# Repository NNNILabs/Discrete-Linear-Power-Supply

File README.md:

# Discrete Linear Power Supply
Fully discrete dual tracking linear supply with CC and CV

## Why?
I was not fully satsified with my previous linear supply based on op-amps, so I decided that I was done with the "black box" approach and decided to go fully discrete this time. 

## How?
The linear supply consists of three parts - the reference, the constant voltage circuit and the constant current circuit. The positive and negative parts are more or less mirror images of each other. 

### The References
The reference element here is a zener diode. The circuit does not operate using reference voltages, but rather reference currents supplied by degenerated PNP/NPN current sources/sinks. 
The Zener diode sets the voltage across the emitter resistors of the buffer transistors, forming current sources/sinks. This current is mirrored and fed back into the Zener diodes, creating a stable closed-loop reference. 

### The Current Limiting Circuitry
The current limiting circuitry is a mix of at least three different circuit ideas from various sources - the emitter input differential amplifier from The Art of Electronics: The X Chapters, the ZDS1009 IC, and the current comparator from Designing Analog Chips. The easiest explanantion is that a constant voltage is set across the left degeneration resistor of the mirror ladder, and when the shunt exceeds this voltage, the output transistor is turned on, pulling the output MOSFET low till the current setpoint is reached. The limit threshold is set by a constant current through the set potentiometer, the voltage across which is mirrored on a resistor which sets the current through the degeneration resistor, the voltage across whic determines the shunt voltage threshold.

### The Voltage Regulating Circuitry 
Again an example of emitter input differential amplifiers - the circuit tries to make the emitter voltages the same and drives the output MOSFET accordingly. The voltage is set by a constant current through the set potentiometer. 

### Notes
- Dual tracking is achieved by sinking/sourcing the same current through the set potentiometers, which creates a voltage across it based on the resistance. Since the current source outputs would otherwise be "floating" (i.e., the voltage across the shunt is constant but there is no guarantee as to where it is relative to ground), two 1M balance resistors connected to ground are added. 
- The value of the compensation resistor and capacitor between the gate and drain of each MOSFET depends on the particular MOSFET type - experiment with different R and C values to get the best compensation, in my case 100nF and 56 Ohms barely worked. 

## Should I make one?
It's up to you - I created this mostly as a challenge but with the hopes of being able to use it - but it was not to be - another "Look, ma! No ICs" circuit bending victim. 
- Oscillations on the output
- Pathetic power supply rejection
- Output voltage drifts randomly

## Conclusion
Some interesting circuit ideas, if you want to pick something up.

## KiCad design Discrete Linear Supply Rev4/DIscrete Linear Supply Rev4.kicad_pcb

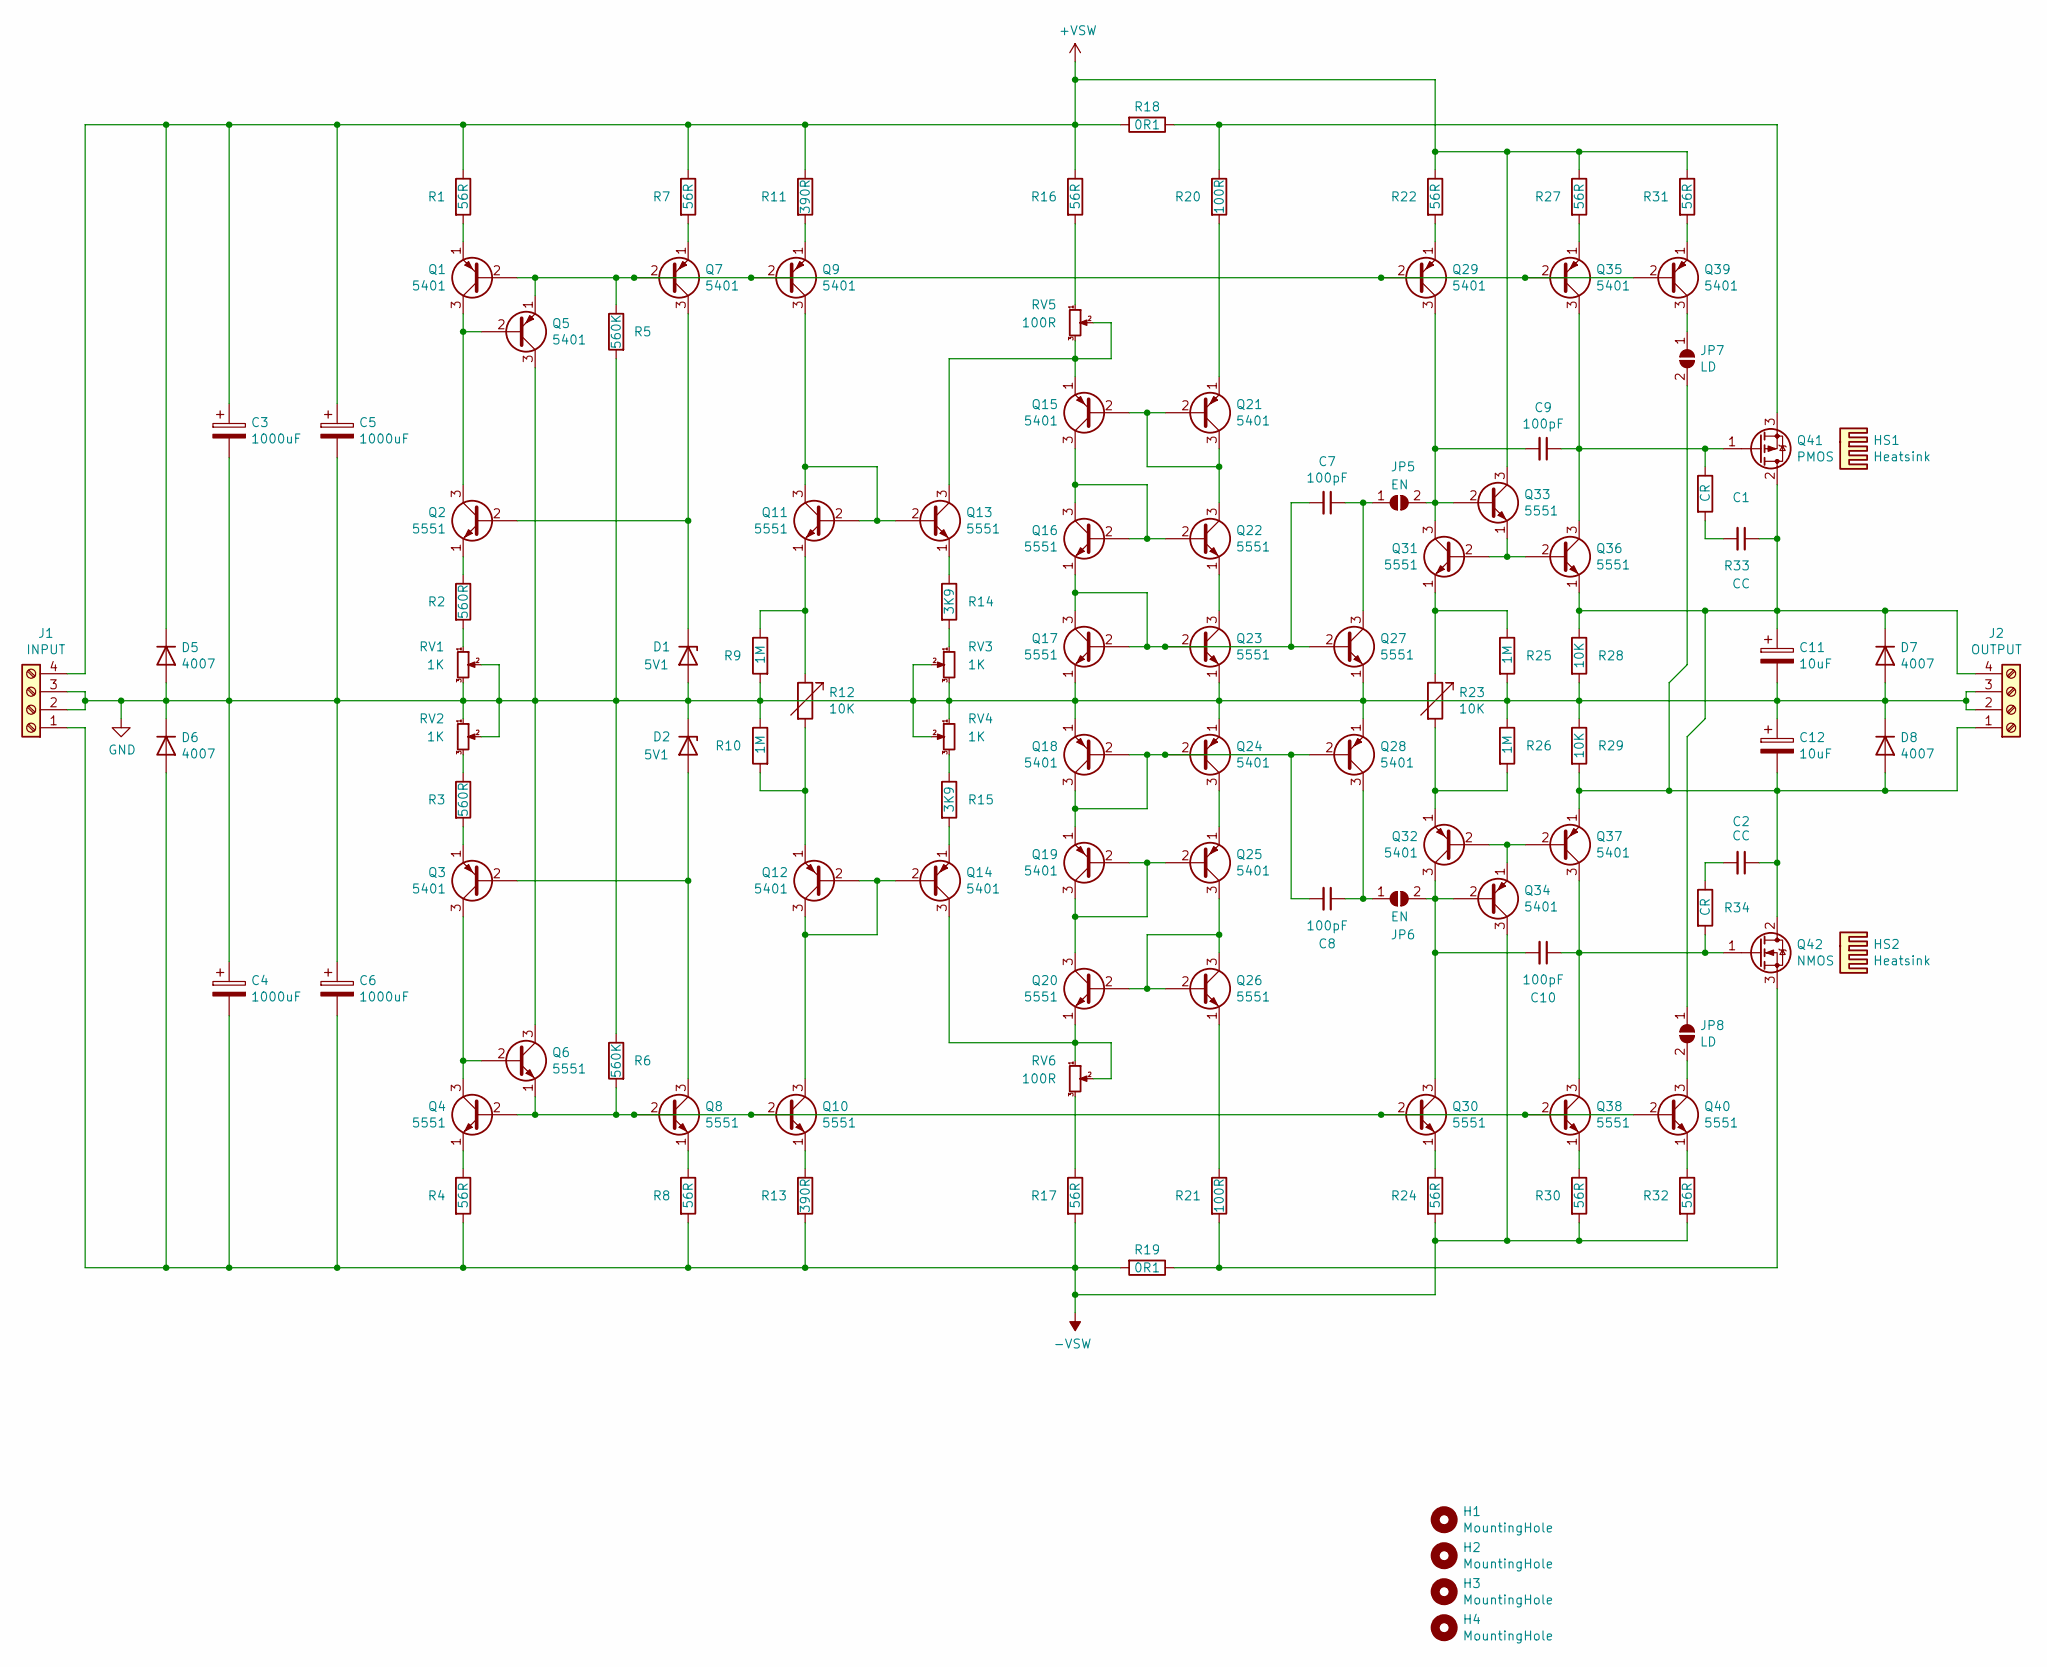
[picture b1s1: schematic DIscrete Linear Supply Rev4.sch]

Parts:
C1, C2: CC; C_Disc_D3.8mm_W2.6mm_P2.50mm
C3, C4, C5, C6: 1000uF; CP_Radial_D16.0mm_P7.50mm
C7, C8, C9, C10: 100pF; C_Disc_D3.8mm_W2.6mm_P2.50mm
C11, C12: 10uF; CP_Radial_D8.0mm_P5.00mm
D1, D2: 5V1; D_DO-41_SOD81_P10.16mm_Horizontal
D5, D6, D7, D8: 4007; D_DO-41_SOD81_P10.16mm_Horizontal
H1, H2, H3, H4: MountingHole; MountingHole_3.2mm_M3_Pad_Via
HS1, HS2: Heatsink; Heatsink_Fischer_SK104-STCB_35x13mm__2xDrill3.5mm_ScrewM3
J1: INPUT; TerminalBlock_bornier-4_P5.08mm
J2: OUTPUT; TerminalBlock_bornier-4_P5.08mm
JP5, JP6: EN; SolderJumper-2_P1.3mm_Open_RoundedPad1.0x1.5mm
JP7, JP8: LD; SolderJumper-2_P1.3mm_Open_RoundedPad1.0x1.5mm
Q1, Q3, Q5, Q7, Q9, Q12, Q14, Q15, Q18, Q19, Q21, Q24, Q25, Q28, Q29, Q32, Q34, Q35, Q37, Q39: 5401; TO-92L_Inline_Wide
Q2, Q4, Q6, Q8, Q10, Q11, Q13, Q16, Q17, Q20, Q22, Q23, Q26, Q27, Q30, Q31, Q33, Q36, Q38, Q40: 5551; TO-92L_Inline_Wide
Q41: PMOS; TO-220-3_Vertical
Q42: NMOS; TO-220-3_Vertical
R1, R4, R7, R8, R16, R17, R22, R24, R27, R30, R31, R32: 56R; R_Axial_DIN0207_L6.3mm_D2.5mm_P10.16mm_Horizontal
R2, R3: 560R; R_Axial_DIN0207_L6.3mm_D2.5mm_P10.16mm_Horizontal
R5, R6: 560K; R_Axial_DIN0207_L6.3mm_D2.5mm_P10.16mm_Horizontal
R9, R10, R25, R26: 1M; R_Axial_DIN0207_L6.3mm_D2.5mm_P10.16mm_Horizontal
R11, R13: 390R; R_Axial_DIN0207_L6.3mm_D2.5mm_P10.16mm_Horizontal
R12, R23: 10K; PinHeader_1x02_P2.54mm_Vertical
R14, R15: 3K9; R_Axial_DIN0207_L6.3mm_D2.5mm_P10.16mm_Horizontal
R18, R19: 0R1; R_Axial_DIN0414_L11.9mm_D4.5mm_P20.32mm_Horizontal
R20, R21: 100R; R_Axial_DIN0207_L6.3mm_D2.5mm_P10.16mm_Horizontal
R28, R29: 10K; R_Axial_DIN0207_L6.3mm_D2.5mm_P10.16mm_Horizontal
R33, R34: CR; R_Axial_DIN0207_L6.3mm_D2.5mm_P10.16mm_Horizontal
RV1, RV2, RV3, RV4: 1K; Potentiometer_Bourns_3296W_Vertical
RV5, RV6: 100R; Potentiometer_Bourns_3296W_Vertical

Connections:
unnamed: C1.2, R33.2
unnamed: C2.2, R34.1
unnamed: C7.1, JP5.1 (A), Q27.3 (C)
unnamed: C7.2, Q16.1 (E), Q17.2 (B), Q17.3 (C), Q23.2 (B), Q27.2 (B)
unnamed: C8.1, JP6.1 (A), Q28.3 (C)
unnamed: C8.2, Q18.2 (B), Q18.3 (C), Q19.1 (E), Q24.2 (B), Q28.2 (B)
unnamed: C9.1, Q35.3 (C), Q36.3 (C), Q41.1 (G), R33.1
unnamed: C9.2, JP5.2 (B), Q29.3 (C), Q31.3 (C), Q33.2 (B)
unnamed: C10.1, Q37.3 (C), Q38.3 (C), Q42.1 (G), R34.2
unnamed: C10.2, JP6.2 (B), Q30.3 (C), Q32.3 (C), Q34.2 (B)
unnamed: C1.1, C11.1, D7.1 (K), J2.4, JP8.1 (A), Q36.1 (E), Q41.2 (D), R28.1
unnamed: C2.1, C12.2, D8.2 (A), J2.1, JP7.2 (B), Q37.1 (E), Q42.2 (D), R29.2
unnamed: D1.1 (K), Q2.2 (B), Q7.3 (C)
unnamed: D2.2 (A), Q3.2 (B), Q8.3 (C)
unnamed: JP7.1 (A), Q39.3 (C)
unnamed: JP8.2 (B), Q40.3 (C)
unnamed: Q1.1 (E), R1.2
unnamed: Q1.2 (B), Q5.1 (E), Q7.2 (B), Q9.2 (B), Q29.2 (B), Q35.2 (B), Q39.2 (B), R5.1
unnamed: Q1.3 (C), Q2.3 (C), Q5.2 (B)
unnamed: Q2.1 (E), R2.1
unnamed: Q3.1 (E), R3.2
unnamed: Q3.3 (C), Q4.3 (C), Q6.2 (B)
unnamed: Q4.1 (E), R4.1
unnamed: Q7.1 (E), R7.2
unnamed: Q8.1 (E), R8.1
unnamed: Q9.1 (E), R11.2
unnamed: Q10.1 (E), R13.1
unnamed: Q4.2 (B), Q6.1 (E), Q8.2 (B), Q10.2 (B), Q30.2 (B), Q38.2 (B), Q40.2 (B), R6.2
unnamed: Q10.3 (C), Q12.2 (B), Q12.3 (C), Q14.2 (B)
unnamed: Q11.1 (E), R9.1, R12.1
unnamed: Q9.3 (C), Q11.2 (B), Q11.3 (C), Q13.2 (B)
unnamed: Q12.1 (E), R10.2, R12.2
unnamed: Q13.1 (E), R14.1
unnamed: Q13.3 (C), Q15.1 (E), RV5.2, RV5.3
unnamed: Q14.1 (E), R15.2
unnamed: Q14.3 (C), Q20.1 (E), RV6.1, RV6.2
unnamed: Q15.2 (B), Q21.2 (B), Q21.3 (C), Q22.3 (C)
unnamed: Q15.3 (C), Q16.2 (B), Q16.3 (C), Q22.2 (B)
unnamed: Q19.2 (B), Q19.3 (C), Q20.3 (C), Q25.2 (B)
unnamed: Q20.2 (B), Q25.3 (C), Q26.2 (B), Q26.3 (C)
unnamed: Q21.1 (E), R20.2
unnamed: Q22.1 (E), Q23.3 (C)
unnamed: Q24.3 (C), Q25.1 (E)
unnamed: Q26.1 (E), R21.1
unnamed: Q29.1 (E), R22.2
unnamed: Q30.1 (E), R24.1
unnamed: Q31.1 (E), R23.1, R25.1
unnamed: Q31.2 (B), Q33.1 (E), Q36.2 (B)
unnamed: Q32.1 (E), R23.2, R26.2
unnamed: Q32.2 (B), Q34.1 (E), Q37.2 (B)
unnamed: Q35.1 (E), R27.2
unnamed: Q38.1 (E), R30.1
unnamed: Q39.1 (E), R31.2
unnamed: Q40.1 (E), R32.1
unnamed: Q41.3 (S), R18.1, R20.1
unnamed: Q42.3 (S), R19.1, R21.2
unnamed: R2.2, RV1.1
unnamed: R3.1, RV2.3
unnamed: R14.2, RV3.1
unnamed: R15.1, RV4.3
unnamed: R16.2, RV5.1
unnamed: R17.1, RV6.3

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
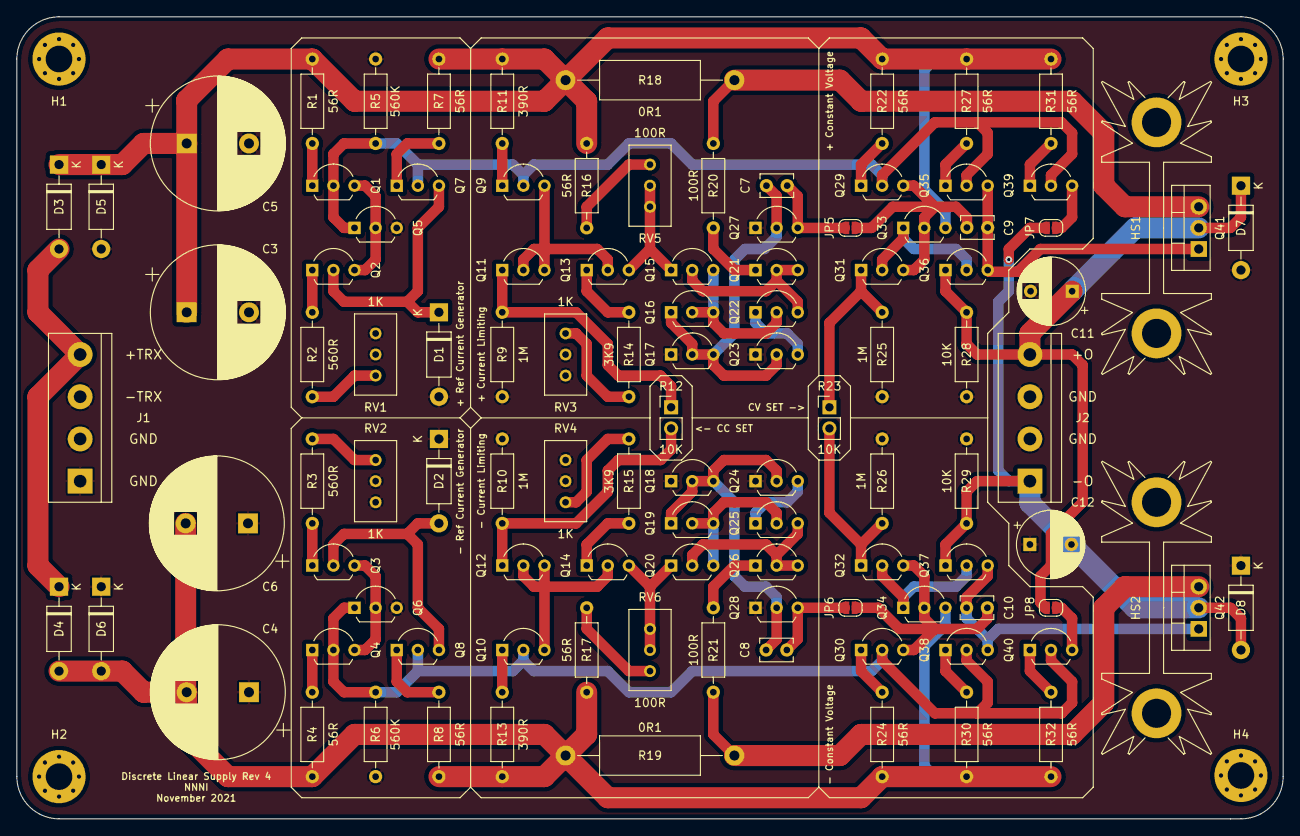
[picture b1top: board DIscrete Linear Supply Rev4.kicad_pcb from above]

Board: 2 copper layers, 152.4 x 96.5 mm, 110 parts (0 on the bottom side), 64 nets.

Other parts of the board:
D3, D4: 4007; D_DO-41_SOD81_P10.16mm_Horizontal

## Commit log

2021-12-02 hardware files, compensation not added yet
2021-12-04 schematics up-to-date
